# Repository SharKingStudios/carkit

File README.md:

# CarKit – Because Your RC Car Needs a Brain  

### A Swiss-Army-Knife Control Board for DIY RC Chaos™  

*(You bring the chassis. It brings the brains.)*  

---

## Renders
*Visuals because everyone loves eye candy.*

---

## BOM
All the silicon, blinkenlights, and screw-down bits live **[here](/BOM.csv)**.

**Main characters:**
- **MCU:** ESP32-C3-WROOM-02
- **Motor Driver:** DRV8876 dual DC motor driver
- **5 V Regulator:** LM2596SX-5.0 buck converter
- **3.3 V Regulator:** AMS1117-3.3 LDO
- **RGB LEDs:** SK6812 addressable LEDs (x4)
- **Power LED:** XL-2012UVA
- **Inputs:** USB-C, Barrel jack, and screw terminal power
- **Connectors:** KF301 5.0 mm terminal blocks + 2×3 SMT headers  
- **Misc:** Buttons, buzzer, pull-ups, decoupling caps, and the usual supporting cast  

(See `BOM.md` for the full part list, values, and LCSC links.)

---

## What is this?

This is a **do-it-all RC control board** built around an **ESP32-C3**, designed to handle basically everything you might want on a DIY RC car:

- **2 DC motors with PWM** (think: **drive** + **steering/turning**)
- **1 BLDC motor output** (via external ESC)
- **1 servo motor output**
- **Bluetooth gamepad support** (so you can use almost any Bluetooth controller)
- **Multiple power input options** (USB-C, barrel jack, or raw battery via screw terminals)
- **4 RGB status LEDs** for connection, mode, and “because RGB”  
- **On-board buzzer** for beeps, alerts, and dramatic startup tones

It’s meant to be the **drop-in brain** for “I duct-taped this together but now I want it to drive nicely” RC builds.

---

## Features

### Motor Control
- **2× DC motor channels**
  - PWM control for speed
  - Direction control via DRV8876
  - Great for **drive + steering** or **tank drive*** setups
- **1× BLDC channel (signal)**
  - Standard PWM output to an external ESC
- **1× Servo output**
  - For steering, camera gimbals, or cursed animatronics
 
<sub>*While the board supports tank drive it wasn't built for it.</sub>

### Power Options
Because every DIY RC build uses a *different* battery, obviously.

- **USB-C (5 V)**
  - For bench testing, firmware dev, and flexing modern ports
- **Barrel jack**
  - Perfect for **9 V batteries** or standard DC wall adapters
- **Screw terminals**
  - Bring your own LiPo / battery pack
- **On-board power handling:**
  - **LM2596SX-5.0** buck converts input to 5 V
  - **AMS1117-3.3** steps 5 V down to 3.3 V for the ESP32-C3
  - Bulk and decoupling caps sprinkled everywhere to keep noise and brownouts away
  
*(Dont feed the board anything over 36V, I would recommend staying under 24V)*

### LEDs & Buttons
- **4× SK6812 RGB LEDs**
  - Can show:
    - **Connection status** (paired / searching / sad)
    - **Board mode** (e.g. normal, config, debug)
    - **User-defined patterns** (rainbow, brake lights, underglow, whatever)
- **1× Power LED**
  - Because sometimes you just need “is this thing on?”
- **Tactile buttons**
  - For reset and boot functions (programming)

### Connectivity & IO
- **ESP32-C3 MCU**
  - **Wi-Fi + Bluetooth LE**
  - Extra GPIOs broken out via **2×3 SMT headers** for expansion
- **Screw terminal outputs**
  - For motors, power, and other “don’t-come-loose” connections

---

## Motor Channels Overview  

| Channel     | Type        | Typical Use              | Notes                                   |
|-------------|-------------|--------------------------|-----------------------------------------|
| M1          | DC Motor    | Main Drive               | PWM + DIR via DRV8876                   |
| M2          | DC Motor    | Turning / Steering       | PWM + DIR via DRV8876                   |
| BLDC OUT    | PWM Signal  | Brushless ESC Input      | External ESC drives the BLDC motor      |
| SERVO OUT   | Servo PWM   | Steering / Gimbal / Etc. | Standard RC-style servo signal          |

---

## How It Works

At a high level:

1. **You power the board** via USB-C, barrel jack, or screw terminals.  
2. The **LM2596** generates a solid 5 V rail, and the **AMS1117** creates the 3.3 V rail for the ESP32-C3.  
3. The **ESP32-C3** runs your firmware:
   - Reads input from a **Bluetooth controller**
   - Outputs PWM and direction signals to the **DRV8876** for the DC motors  
   - Generates PWM for the **BLDC ESC** and **servo**  
   - Drives the **SK6812 RGB LEDs** and **buzzer** to show status and vibes  

All the “annoying parts” (power, drivers, IO protection, connectors, etc.) are on the PCB, so you can focus on mechanical design.

---

## Using a Bluetooth Controller

The exact firmware and controller mapping is up to you and some basic stuff is included, but the general idea is:

1. Flash your ESP32-C3 firmware that:
   - Pairs with a **Bluetooth gamepad / controller**
   - Maps sticks/triggers/buttons to motor speeds and steering
2. On startup, the **RGB LEDs** can:
   - Pulse / chase while waiting for a controller  
   - Turn solid once connected  
3. Drive your RC car like a normal RC car, but with way more flexibility and hackability.

*(You can map “A” to beep the buzzer. You absolutely should.)*

---

## RGB LEDs  

Because a control board without RGB is just morally wrong.

Possible roles for the **4 SK6812 LEDs**:

- **LED 1 – Connection status (Bluetooth)**  
- **LED 2 – Mode indicator (normal / config / debug)**  
- **LED 3-4 – User bling (animations, underglow, warnings, etc.)**

Or ignore all that and just run full rainbow vomit. No judgment.

---

## Why?  

This board exists for that moment when you’ve got:

- An RC chassis
- Some motors
- A pile of batteries
- And zero desire to reinvent **“basic motor control + power + Bluetooth”** *again*

It’s meant to be the **one board** that handles:
- Motors
- Power
- Input
- Feedback

…so you can just design something cool and let this handle the boring electronics.

---

## Contribute  

Have ideas? Want a new connector, mode, sample firmware, or just want to roast my layout?

- Open an **issue**
- Submit a **PR**
- Or just yell at me on GitHub with suggestions

---

## Disclaimer  

This project is open-source, powered by **vibes**, and tested mostly on my own questionable hardware.  

If you:
- Overvolt it  
- Reverse the battery  
- Strap it to a rocket  
- Or send 48 V into something that wanted 5 V  

…and it smokes, explodes, or develops sentience, that’s **entirely on you.**

Happy hacking!

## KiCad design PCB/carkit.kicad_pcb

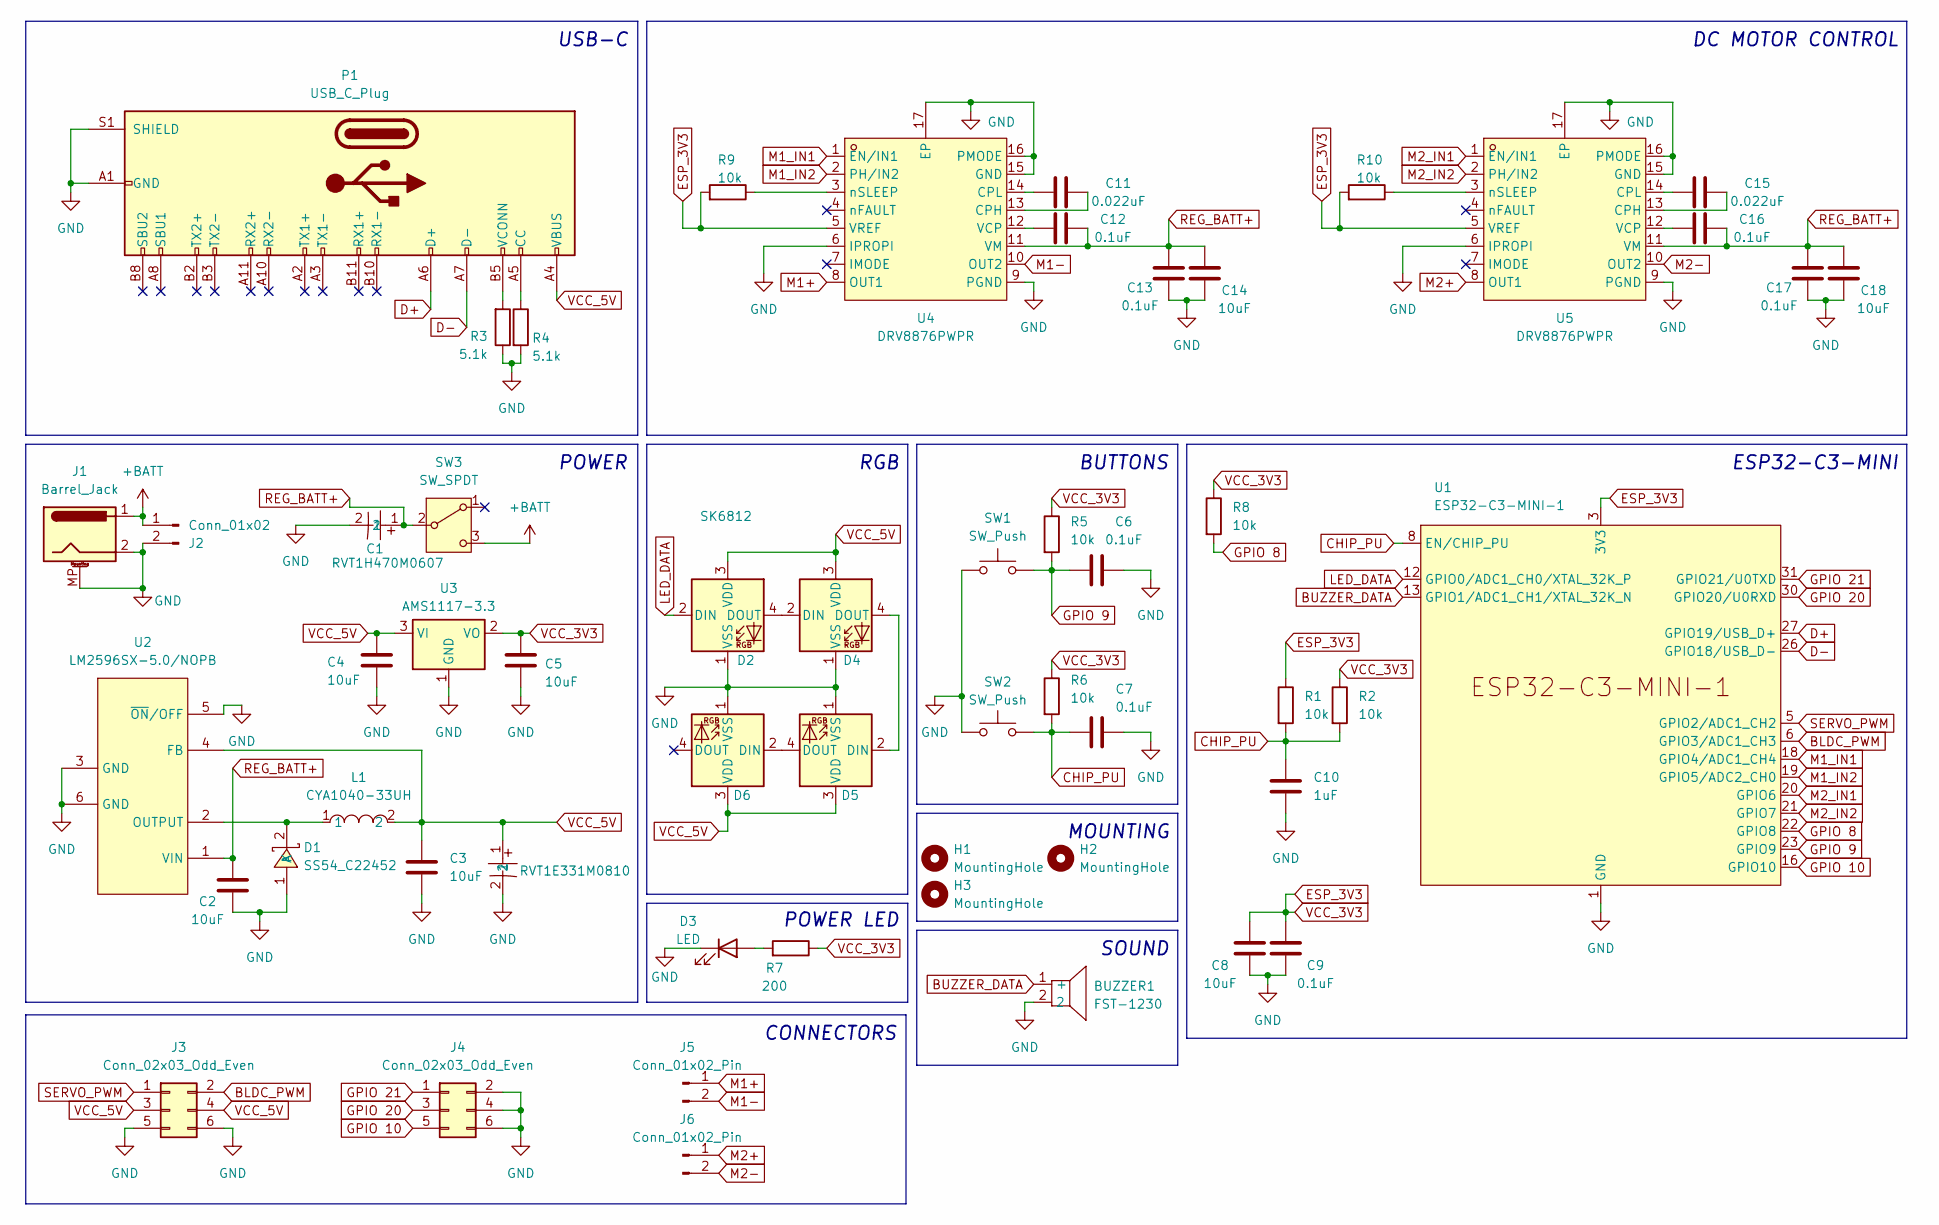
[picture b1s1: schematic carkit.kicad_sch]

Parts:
BUZZER1: FST-1230; BUZ-SMD_L12.0-W12.0_FUET-1230; LCSC Part C391037
C1: RVT1H470M0607; CAP-SMD_BD6.3-L6.6-W6.6-LS7.6-FD; LCSC Part C72523
C2, C3, C4, C5, C8, C14, C18: 10uF; C0805
C6, C7, C9, C12, C13, C16, C17: 0.1uF; C0805
C10: 1uF; C0805
C11, C15: 0.022uF; C0805
C19: RVT1E331M0810; CAP-SMD_BD8.0-L8.3-W8.3-LS9.3-FD-1; LCSC Part C335985
D1: SS54_C22452; SMA_L4.4-W2.8-LS5.4-R-RD; LCSC Part C22452
D2, D4, D5, D6: SK6812; LED_SK6812_PLCC4_5.0x5.0mm_P3.2mm
D3: LED; LED0805-RD
H1, H2, H3: MountingHole; MountingHole_3.2mm_M3_Pad_Via
J1: Barrel_Jack; DC-IN-TH_DC-005-A200
J2: Conn_01x02; CONN-TH_P5.00_KF301-5.0-2P
J3, J4: Conn_02x03_Odd_Even; HDR-SMD_6P-P2.54-V
J5, J6: Conn_01x02_Pin; CONN-TH_P5.00_KF301-5.0-2P
L1: CYA1040-33UH; IND-SMD_L11.6-W10.1; LCSC Part C6364680
P1: USB_C_Plug; USB-C_SMD-TYPE-C-31-M-12
R1, R2, R5, R6, R8, R9, R10: 10k; R0805
R3, R4: 5.1k; R0805
R7: 200; R0805
SW1, SW2: SW_Push; SW-SMD_L3.9-W3.0-P4.45
SW3: SW_SPDT; SW-SMD_MST-12D18G4-SPDT-SLIDE-SWITCH
U1: ESP32-C3-MINI-1
U2: LM2596SX-5.0/NOPB; TO-263-5_L10.2-W8.9-P1.70-TL; LCSC Part C10002
U3: AMS1117-3.3; SOT-223-3_TabPin2
U4, U5: DRV8876PWPR; HTSSOP-16_L5.0-W4.4-P0.65-LS6.4-BL-EP; LCSC Part C575551

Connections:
+BATT: J1.1, J2.1, SW3.3 (C)
BLDC_PWM: J3.2, U1.6 (GPIO3/ADC1_CH3)
BUZZER_DATA: BUZZER1.1 (+), U1.13 (GPIO1/ADC1_CH1/XTAL_32K_N)
CHIP_PU: C7.1, C10.1, R1.2, R2.2, R6.2, SW2.1, U1.8 (EN/CHIP_PU)
D+: P1.A6 (D+), U1.27 (GPIO19/USB_D+)
D-: P1.A7 (D-), U1.26 (GPIO18/USB_D-)
ESP_3V3: C5.1, C8.2, C9.2, R1.1, R2.1, R5.1, R6.1, R7.1, R8.1, R9.2, R10.2, U1.3 (3V3), U3.2 (VO), U4.5 (VREF), U5.5 (VREF)
GND: BUZZER1.2, C1.2, C2.1, C3.2, C4.2, C5.2, C6.2, C7.2, C8.1, C9.1, C10.2, C13.1, C14.1, C17.1, C18.1, C19.2, D1.1 (A), D2.1 (VSS), D3.1 (K), D4.1 (VSS), D5.1 (VSS), D6.1 (VSS), J1.2, J1.MP (MountPin), J2.2, J3.5, J3.6, J4.2, J4.4, J4.6, P1.A1 (GND), P1.A12 (GND), P1.B1 (GND), P1.B12 (GND), P1.S1 (SHIELD), R3.1, R4.2, SW1.2, SW2.2, U1.1 (GND), U1.2 (GND), U1.11 (GND), U1.14 (GND), U1.36 (GND), U1.37 (GND), U1.38 (GND), U1.39 (GND), U1.40 (GND), U1.41 (GND), U1.42 (GND), U1.43 (GND), U1.44 (GND), U1.45 (GND), U1.46 (GND), U1.47 (GND), U1.48 (GND), U1.49 (GND), U1.50 (GND), U1.51 (GND), U1.52 (GND), U1.53 (GND), U2.3 (GND), U2.5 (~ON/OFF), U2.6 (GND), U3.1 (GND), U4.6 (IPROPI), U4.9 (PGND), U4.15 (GND), U4.16 (PMODE), U4.17 (EP), U5.6 (IPROPI), U5.9 (PGND), U5.15 (GND), U5.16 (PMODE), U5.17 (EP)
GPIO 8: R8.2, U1.22 (GPIO8)
GPIO 9: C6.1, R5.2, SW1.1, U1.23 (GPIO9)
GPIO 10: J4.5, U1.16 (GPIO10)
GPIO 20: J4.3, U1.30 (GPIO20/U0RXD)
GPIO 21: J4.1, U1.31 (GPIO21/U0TXD)
LED_DATA: D2.2 (DIN), U1.12 (GPIO0/ADC1_CH0/XTAL_32K_P)
M1+: J5.1, U4.8 (OUT1)
M1-: J5.2, U4.10 (OUT2)
M1_IN1: U1.18 (GPIO4/ADC1_CH4), U4.1 (EN/IN1)
M1_IN2: U1.19 (GPIO5/ADC2_CH0), U4.2 (PH/IN2)
M2+: J6.1, U5.8 (OUT1)
M2-: J6.2, U5.10 (OUT2)
M2_IN1: U1.20 (GPIO6), U5.1 (EN/IN1)
M2_IN2: U1.21 (GPIO7), U5.2 (PH/IN2)
unnamed: D1.2 (K), L1.1, U2.2 (OUTPUT)
unnamed: D2.4 (DOUT), D4.2 (DIN)
unnamed: D3.2 (A), R7.2
unnamed: D4.4 (DOUT), D5.2 (DIN)
unnamed: D5.4 (DOUT), D6.2 (DIN)
unnamed: P1.A5 (CC), R4.1
unnamed: P1.B5 (VCONN), R3.2
unnamed: C11.1, U4.13 (CPH)
unnamed: C11.2, U4.14 (CPL)
unnamed: C12.2, U4.12 (VCP)
unnamed: R9.1, U4.3 (nSLEEP)
unnamed: C15.1, U5.13 (CPH)
unnamed: C15.2, U5.14 (CPL)
unnamed: C16.2, U5.12 (VCP)
unnamed: R10.1, U5.3 (nSLEEP)
REG_BATT+: C1.1, C2.2, C12.1, C13.2, C14.2, C16.1, C17.2, C18.2, SW3.2 (B), U2.1 (VIN), U4.11 (VM), U5.11 (VM)
SERVO_PWM: J3.1, U1.5 (GPIO2/ADC1_CH2)
VCC_5V: C3.1, C4.1, C19.1, D2.3 (VDD), D4.3 (VDD), D5.3 (VDD), D6.3 (VDD), J3.3, J3.4, L1.2, P1.A4 (VBUS), P1.A9 (VBUS), P1.B4 (VBUS), P1.B9 (VBUS), U2.4 (FB), U3.3 (VI)

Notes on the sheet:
MOUNTING
POWER
CONNECTORS
BUTTONS
USB-C
ESP32-C3-MINI
POWER LED
RGB
DC MOTOR CONTROL
SOUND

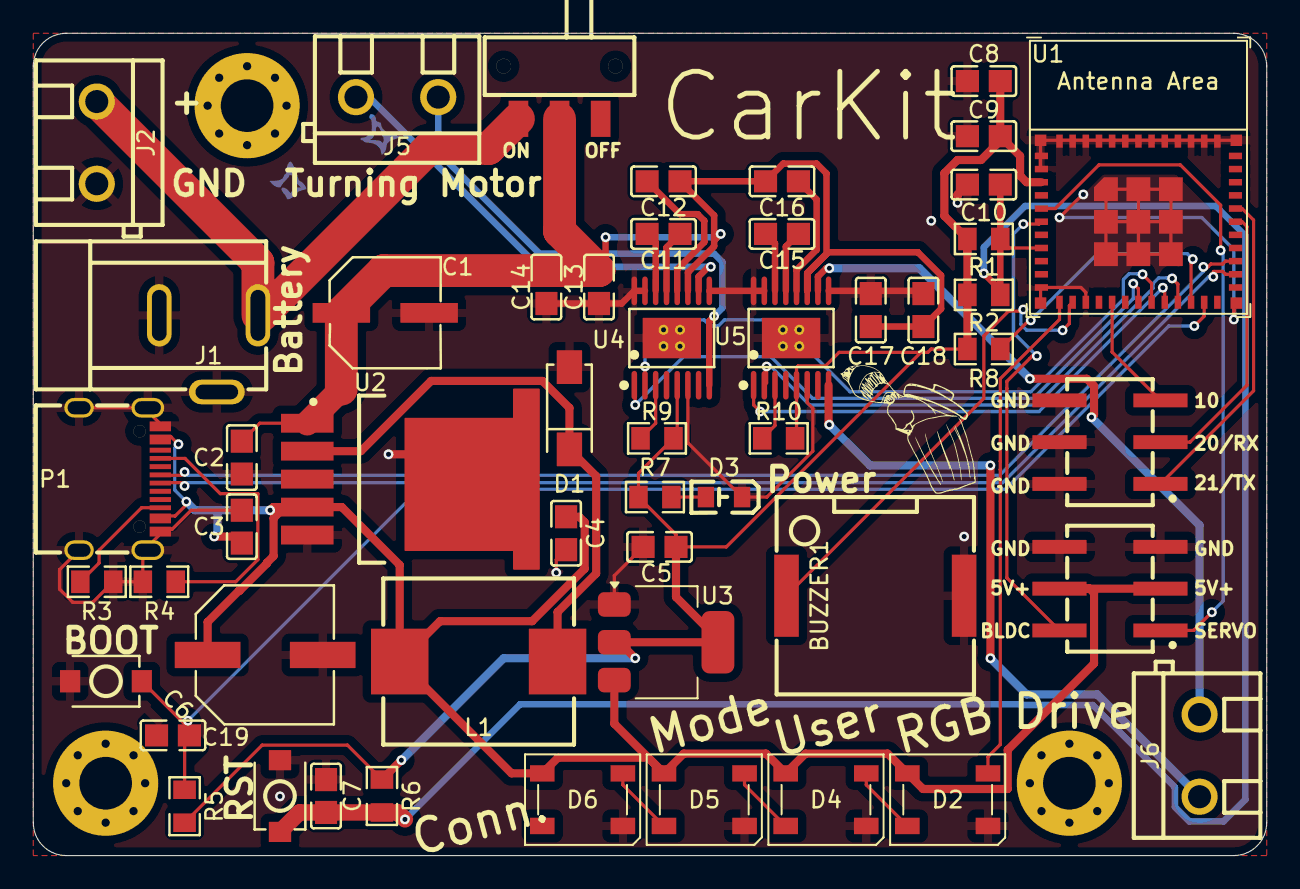
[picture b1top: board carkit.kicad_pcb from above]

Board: 2 copper layers, 75.0 x 50.0 mm, 55 parts (0 on the bottom side), 40 nets.

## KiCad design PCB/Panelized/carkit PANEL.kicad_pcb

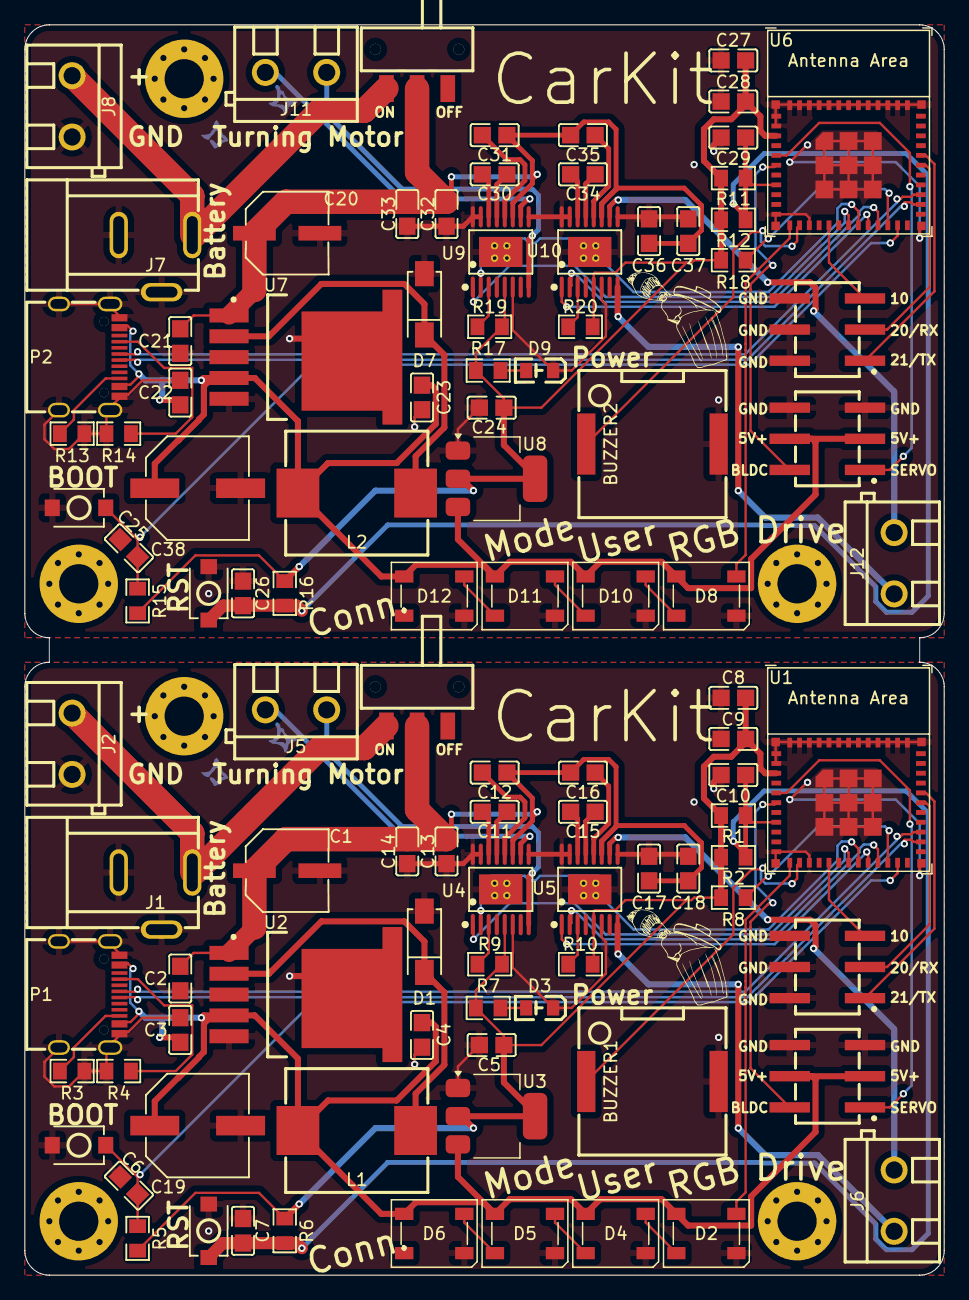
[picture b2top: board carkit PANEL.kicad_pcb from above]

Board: 2 copper layers, 75.0 x 102.0 mm, 110 parts (0 on the bottom side), 40 nets.

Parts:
BUZZER1, BUZZER2: FST-1230; BUZ-SMD_L12.0-W12.0_FUET-1230
C1, C20: RVT1H470M0607; CAP-SMD_BD6.3-L6.6-W6.6-LS7.6-FD
C2, C3, C4, C5, C8, C14, C18, C21, C22, C23, C24, C27, C33, C37: 10uF; C0805
C6, C7, C9, C12, C13, C16, C17, C25, C26, C28, C31, C32, C35, C36: 0.1uF; C0805
C10, C29: 1uF; C0805
C11, C15, C30, C34: 0.022uF; C0805
C19, C38: RVT1E331M0810; CAP-SMD_BD8.0-L8.3-W8.3-LS9.3-FD-1
D1, D7: SS54_C22452; SMA_L4.4-W2.8-LS5.4-R-RD
D2, D4, D5, D6, D8, D10, D11, D12: SK6812; LED_SK6812_PLCC4_5.0x5.0mm_P3.2mm
D3, D9: LED; LED0805-RD
H1, H2, H3, H4, H5, H6: MountingHole; MountingHole_3.2mm_M3_Pad_Via
J1, J7: Barrel_Jack; DC-IN-TH_DC-005-A200
J2, J8: Conn_01x02; CONN-TH_P5.00_KF301-5.0-2P
J3, J4, J9, J10: Conn_02x03_Odd_Even; HDR-SMD_6P-P2.54-V
J5, J6, J11, J12: Conn_01x02_Pin; CONN-TH_P5.00_KF301-5.0-2P
L1, L2: CYA1040-33UH; IND-SMD_L11.6-W10.1
P1, P2: USB_C_Plug; USB-C_SMD-TYPE-C-31-M-12
R1, R2, R5, R6, R8, R9, R10, R11, R12, R15, R16, R18, R19, R20: 10k; R0805
R3, R4, R13, R14: 5.1k; R0805
R7, R17: 200; R0805
SW1, SW2, SW4, SW5: SW_Push; SW-SMD_L3.9-W3.0-P4.45
SW3, SW6: SW_SPDT; SW-SMD_MST-12D18G4-SPDT-SLIDE-SWITCH
U1, U6: ESP32-C3-MINI-1
U2, U7: LM2596SX-5.0/NOPB; TO-263-5_L10.2-W8.9-P1.70-TL
U3, U8: AMS1117-3.3; SOT-223-3_TabPin2
U4, U5, U9, U10: DRV8876PWPR; HTSSOP-16_L5.0-W4.4-P0.65-LS6.4-BL-EP

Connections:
+BATT: J1.1, J2.1, J7.1, J8.1, SW3.3 (C), SW6.3 (C)
BLDC_PWM: J3.2, J9.2, U1.6 (GPIO3/ADC1_CH3), U6.6 (GPIO3/ADC1_CH3)
BUZZER_DATA: BUZZER1.1 (+), BUZZER2.1 (+), U1.13 (GPIO1/ADC1_CH1/XTAL_32K_N), U6.13 (GPIO1/ADC1_CH1/XTAL_32K_N)
CHIP_PU: C7.1, C10.1, C26.1, C29.1, R1.2, R2.2, R6.2, R11.2, R12.2, R16.2, SW2.1, SW5.1, U1.8 (EN/CHIP_PU), U6.8 (EN/CHIP_PU)
D+: P1.A6 (D+), P2.A6 (D+), U1.27 (GPIO19/USB_D+), U6.27 (GPIO19/USB_D+)
D-: P1.A7 (D-), P2.A7 (D-), U1.26 (GPIO18/USB_D-), U6.26 (GPIO18/USB_D-)
ESP_3V3: C5.1, C8.2, C9.2, C24.1, C27.2, C28.2, R1.1, R2.1, R5.1, R6.1, R7.1, R8.1, R9.2, R10.2, R11.1, R12.1, R15.1, R16.1, R17.1, R18.1, R19.2, R20.2, U1.3 (3V3), U3.2 (VO), U4.5 (VREF), U5.5 (VREF), U6.3 (3V3), U8.2 (VO), U9.5 (VREF), U10.5 (VREF)
GND: BUZZER1.2, BUZZER2.2, C1.2, C2.1, C3.2, C4.2, C5.2, C6.2, C7.2, C8.1, C9.1, C10.2, C13.1, C14.1, C17.1, C18.1, C19.2, C20.2, C21.1, C22.2, C23.2, C24.2, C25.2, C26.2, C27.1, C28.1, C29.2, C32.1, C33.1, C36.1, C37.1, C38.2, D1.1 (A), D2.1 (VSS), D3.1 (K), D4.1 (VSS), D5.1 (VSS), D6.1 (VSS), D7.1 (A), D8.1 (VSS), D9.1 (K), D10.1 (VSS), D11.1 (VSS), D12.1 (VSS), J1.2, J1.MP (MountPin), J2.2, J3.5, J3.6, J4.2, J4.4, J4.6, J7.2, J7.MP (MountPin), J8.2, J9.5, J9.6, J10.2, J10.4, J10.6, P1.A1 (GND), P1.A12 (GND), P1.B1 (GND), P1.B12 (GND), P1.S1 (SHIELD), P2.A1 (GND), P2.A12 (GND), P2.B1 (GND), P2.B12 (GND), P2.S1 (SHIELD), R3.1, R4.2, R13.1, R14.2, SW1.2, SW2.2, SW4.2, SW5.2, U1.1 (GND), U1.2 (GND), U1.11 (GND), U1.14 (GND), U1.36 (GND), U1.37 (GND), U1.38 (GND), U1.39 (GND), U1.40 (GND), U1.41 (GND), U1.42 (GND), U1.43 (GND), U1.44 (GND), U1.45 (GND), U1.46 (GND), U1.47 (GND), U1.48 (GND), U1.49 (GND), U1.50 (GND), U1.51 (GND), U1.52 (GND), U1.53 (GND), U2.3 (GND), U2.5 (~ON/OFF), U2.6 (GND), U3.1 (GND), U4.6 (IPROPI), U4.9 (PGND), U4.15 (GND), U4.16 (PMODE), U4.17 (EP), U5.6 (IPROPI), U5.9 (PGND), U5.15 (GND), U5.16 (PMODE), U5.17 (EP), U6.1 (GND), U6.2 (GND), U6.11 (GND), U6.14 (GND), U6.36 (GND), U6.37 (GND), U6.38 (GND), U6.39 (GND), U6.40 (GND), U6.41 (GND), U6.42 (GND), U6.43 (GND), U6.44 (GND), U6.45 (GND), U6.46 (GND), U6.47 (GND), U6.48 (GND), U6.49 (GND), U6.50 (GND), U6.51 (GND), U6.52 (GND), U6.53 (GND), U7.3 (GND), U7.5 (~ON/OFF), U7.6 (GND), U8.1 (GND), U9.6 (IPROPI), U9.9 (PGND), U9.15 (GND), U9.16 (PMODE), U9.17 (EP), U10.6 (IPROPI), U10.9 (PGND), U10.15 (GND), U10.16 (PMODE), U10.17 (EP)
GPIO 8: R8.2, R18.2, U1.22 (GPIO8), U6.22 (GPIO8)
GPIO 9: C6.1, C25.1, R5.2, R15.2, SW1.1, SW4.1, U1.23 (GPIO9), U6.23 (GPIO9)
GPIO 10: J4.5, J10.5, U1.16 (GPIO10), U6.16 (GPIO10)
GPIO 20: J4.3, J10.3, U1.30 (GPIO20/U0RXD), U6.30 (GPIO20/U0RXD)
GPIO 21: J4.1, J10.1, U1.31 (GPIO21/U0TXD), U6.31 (GPIO21/U0TXD)
LED_DATA: D2.2 (DIN), D8.2 (DIN), U1.12 (GPIO0/ADC1_CH0/XTAL_32K_P), U6.12 (GPIO0/ADC1_CH0/XTAL_32K_P)
M1+: J5.1, J11.1, U4.8 (OUT1), U9.8 (OUT1)
M1-: J5.2, J11.2, U4.10 (OUT2), U9.10 (OUT2)
M1_IN1: U1.18 (GPIO4/ADC1_CH4), U4.1 (EN/IN1), U6.18 (GPIO4/ADC1_CH4), U9.1 (EN/IN1)
M1_IN2: U1.19 (GPIO5/ADC2_CH0), U4.2 (PH/IN2), U6.19 (GPIO5/ADC2_CH0), U9.2 (PH/IN2)
M2+: J6.1, J12.1, U5.8 (OUT1), U10.8 (OUT1)
M2-: J6.2, J12.2, U5.10 (OUT2), U10.10 (OUT2)
M2_IN1: U1.20 (GPIO6), U5.1 (EN/IN1), U6.20 (GPIO6), U10.1 (EN/IN1)
M2_IN2: U1.21 (GPIO7), U5.2 (PH/IN2), U6.21 (GPIO7), U10.2 (PH/IN2)
unnamed: D1.2 (K), D7.2 (K), L1.1, L2.1, U2.2 (OUTPUT), U7.2 (OUTPUT)
unnamed: D2.4 (DOUT), D4.2 (DIN), D8.4 (DOUT), D10.2 (DIN)
unnamed: D3.2 (A), D9.2 (A), R7.2, R17.2
unnamed: D4.4 (DOUT), D5.2 (DIN), D10.4 (DOUT), D11.2 (DIN)
unnamed: D5.4 (DOUT), D6.2 (DIN), D11.4 (DOUT), D12.2 (DIN)
unnamed: P1.A5 (CC), P2.A5 (CC), R4.1, R14.1
unnamed: P1.B5 (VCONN), P2.B5 (VCONN), R3.2, R13.2
unnamed: C11.1, C30.1, U4.13 (CPH), U9.13 (CPH)
unnamed: C11.2, C30.2, U4.14 (CPL), U9.14 (CPL)
unnamed: C12.2, C31.2, U4.12 (VCP), U9.12 (VCP)
unnamed: R9.1, R19.1, U4.3 (nSLEEP), U9.3 (nSLEEP)
unnamed: C15.1, C34.1, U5.13 (CPH), U10.13 (CPH)
unnamed: C15.2, C34.2, U5.14 (CPL), U10.14 (CPL)
unnamed: C16.2, C35.2, U5.12 (VCP), U10.12 (VCP)
unnamed: R10.1, R20.1, U5.3 (nSLEEP), U10.3 (nSLEEP)
REG_BATT+: C1.1, C2.2, C12.1, C13.2, C14.2, C16.1, C17.2, C18.2, C20.1, C21.2, C31.1, C32.2, C33.2, C35.1, C36.2, C37.2, SW3.2 (B), SW6.2 (B), U2.1 (VIN), U4.11 (VM), U5.11 (VM), U7.1 (VIN), U9.11 (VM), U10.11 (VM)
SERVO_PWM: J3.1, J9.1, U1.5 (GPIO2/ADC1_CH2), U6.5 (GPIO2/ADC1_CH2)
VCC_5V: C3.1, C4.1, C19.1, C22.1, C23.1, C38.1, D2.3 (VDD), D4.3 (VDD), D5.3 (VDD), D6.3 (VDD), D8.3 (VDD), D10.3 (VDD), D11.3 (VDD), D12.3 (VDD), J3.3, J3.4, J9.3, J9.4, L1.2, L2.2, P1.A4 (VBUS), P1.A9 (VBUS), P1.B4 (VBUS), P1.B9 (VBUS), P2.A4 (VBUS), P2.A9 (VBUS), P2.B4 (VBUS), P2.B9 (VBUS), U2.4 (FB), U3.3 (VI), U7.4 (FB), U8.3 (VI)

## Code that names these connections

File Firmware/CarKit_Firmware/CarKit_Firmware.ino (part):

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 * - Bluetooth gamepad (Xbox-compatible) using Bluepad32
 * - DRV8876 (U4 = steering DC, U5 = drive DC)
 * - Optional steering servo + BLDC ESC output
 * - SD6812 / SK6812 / WS2812-compatible LEDs on GPIO0
 * - Piezo buzzer (FST-1230) tones & jingles
 * - Multiple drive modes (car & tank)
 * - Optional debug web UI to edit & persist configuration
 *
 * Pin mapping:
 *   GPIO0  -> SD6812 LED data in  (4 LEDs)
 *   GPIO21 -> broken out, unused
 *   GPIO20 -> broken out, unused
 *   GPIO10 -> broken out, unused
 *   GPIO19 -> USB
 *   GPIO18 -> USB
 *   GPIO2  -> Servo PWM breakout (steering servo)   [optional]
 *   GPIO3  -> BLDC ESC / motor controller PWM       [optional]
 *   GPIO4  -> U4 DRV8876 EN / M1_IN1 (PWM / enable)
 *   GPIO5  -> U4 DRV8876 PH / M1_IN2 (direction)
 *   GPIO6  -> U5 DRV8876 EN / M2_IN1 (PWM / enable)
 *   GPIO7  -> U5 DRV8876 PH / M2_IN2 (direction)
 *
 *   Buzzer FST-1230 -> see BUZZER_PIN below
 *
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const int SERVO_PIN        = 2;   // Steering servo PWM breakout
const int BLDC_ESC_PIN     = 3;   // BLDC ESC PWM breakout

const int U4_EN_PIN        = 4;   // DRV8876 U4 EN / M1_IN1 (PWM / enable)
const int U4_PH_PIN        = 5;   // DRV8876 U4 PH / M1_IN2 (direction)
const int U5_EN_PIN        = 6;   // DRV8876 U5 EN / M2_IN1 (PWM / enable)
const int U5_PH_PIN        = 7;   // DRV8876 U5 PH / M2_IN2 (direction)

// ---- LEDC PWM channels ----
// (Channels are NOT pins – each channel can be attached to one pin.)
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const bool DEFAULT_REVERSE_STEERING_DC  = false;  // reverse U4 direction
const bool DEFAULT_REVERSE_DRIVE_DC     = false;  // reverse U5 direction

const bool DEFAULT_ENABLE_BLDC_OUTPUT   = false;  // ESC on GPIO3
const bool DEFAULT_ENABLE_SERVO_OUTPUT  = true;   // steering servo on GPIO2

// Tank mode: which DRV8876 is LEFT side?
// true  -> U4 = left track, U5 = right track
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</fieldset>

<fieldset><legend>Outputs</legend>
<label><input type="checkbox" name="enServo" VALUE="1" %ENSERVO%> Enable steering servo (GPIO2)</label>
<label><input type="checkbox" name="enBLDC"  VALUE="1" %ENBLDC%> Enable BLDC / ESC output (GPIO3)</label>
<label>Servo center (µs): <input type="number" name="servoCtr" value="%SERVOCTR%" min="1000" max="2000"/></label>
</fieldset>

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
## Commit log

2025-11-23 Schematic mostly complete
    Finished the part selection and the control section of the schematic.
2025-11-24 PCB routing completed
    All components updated and the PCB should be fully functional.
2025-11-24 Panelization Complete
2025-11-24 Renders
2025-11-24 Better Renders
2025-11-24 Initialize README with project details and features
    Added detailed project description, features, and usage instructions for the CarKit RC control board.
2025-11-24 Quick fix
2025-11-24 Update PCB renders
    Refreshed bottom and top PCB render images.
2025-11-24 Restructure Files
2025-11-25 Update BOM
    Updated BOM to use ESP32-C3-WROOM-02-H4, adjusted pricing, and clarified top-up costs.
2025-11-25 Add CarKit firmware
    Added initial CarKit ESP32-C3-MINI firmware which has support for BLE gamepads
2025-11-25 Create README.md for CarKit firmware documentation
    Add comprehensive README for CarKit firmware, detailing features, pin mapping, configuration, and build instructions.
